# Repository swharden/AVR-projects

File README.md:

# AVR-projects
This repository contains a growing collection of individual AVR project files for various tasks. I personally use these projects as starting points for new microcontroller projects, or reference for common procedudures I would otherwise have to go back to the datasheet for (timers, counters, frequency counting or synthesis, interrupts, UART, I2C, ADC, etc). Each folder is self-contained and has batch scripts to set fuses to change the clock source (internal RC oscillator at 8MHz, div/8 for 1MHz, or external crystal typically up to 20 MHz)

**These are some of my favorites:**
> 
- Blink an LED with an [ATTiny45](/ATMega328%20%20LEDblink), [ATTiny2313](ATTiny2313%20%20LEDblink), or [ATMega328](ATMega328%20%20LEDblink)
- sending data from a microcontroller to a PC with USART (likely via USB serial port)
  - [USART for ATTiny2313](ATTiny2313%202017-02-05%20serial%20USART)
  - [ATMega328 wired](ATMega328%202015-01-01%20USART%20serial) or [over bluetooth](ATMega328%202016-09-15%20CVM)
  - [interrupt driven](ATMega328%202015-01-01%20USART%20serial/tx%20rx%20interrupt) vs. [polling method](ATMega328%202015-01-01%20USART%20serial/tx%20rx%20polling) for USART input
- [PWM for ATTiny2313](ATTiny2313%202017-02-01%20PWM) or [PWM for ATTiny85](ATTiny85%202016-12-30%20PWM)
- code to [interface with a rotary encoder](ATTiny2313%202017-02-02%20rotary%20encoder)
- ultra minimal [frequency generator](ATTiny85%202016-07-31%20frequency%20generator) I use for all sorts of stuff
- code to [read ADC values and send them over serial](ATMega328%202017-02-07%20ADC%20serial%20LM35) with ATMega328 (including code for ADC noise reduction mode)

# Programming Setup
I almost always use AVRISPmkII and AVRdude (launched from a batch script) to program my chips. I virtually never use AVRStudio. I typically develop in a Windows environment, but the code (and AVRdude) works the same in Linux.

### Software
* Just install [WinAVR](https://sourceforge.net/projects/winavr/files/) and it should install drivers for common programmers.
* I prefer to edit C code in [Notepad++](https://notepad-plus-plus.org/)
* definitely check out [AVRDudess](http://blog.zakkemble.co.uk/avrdudess-a-gui-for-avrdude/) (a GUI for AVRdude) as an easy GUI to load flash onto chips

### Hardware
* [AVR Programming in 64-bit Windows 7](http://www.swharden.com/wp/2013-05-07-avr-programming-in-64-bit-windows-7/) (should also work for windows 10)
* windows 10 driver for USBTiny is [here](https://learn.adafruit.com/usbtinyisp/drivers)
* actually I only got it to work after installing [Zadig](http://zadig.akeo.ie/)

### Programmers
Note|Picture
---|---
AVRISPmkII is a ceap, fast, and convenient AVR programmer. | 
Bus Pirate _technically_ can program AVRs, but it's so slow it's not practical. [Here's a post](http://www.swharden.com/wp/2016-07-14-controlling-bus-pirate-with-python) I wrote about it. I like the bus pirate when I need to use software to measure voltages and toggle pins. It's slow though, because the handshake it bit-banged and it takes tens of seconds to program an AVR. For just programming, I prefer an (ebay knockoff) AVR ISP mkII. Definately check out AVRDudess as a GUI for AVRDude. I usually get a standard command for a project and put it in a batch file in the same folder.| 
AVRDudess can simplify programming of code and fuses. | 

### Serial Terminal
I highly recommend [RealTerm](https://sourceforge.net/projects/realterm/) for Windows

## Common AVR Datasheets and Pinouts

chip|pinout|datasheets
---|---|---
**ATMega328**||[[summary](http://www.atmel.com/Images/Atmel-42735-8-bit-AVR-Microcontroller-ATmega328-328P_Summary.pdf)] [[complete](http://www.atmel.com/Images/Atmel-42735-8-bit-AVR-Microcontroller-ATmega328-328P_Datasheet.pdf)]
**ATTiny2313**||[[summary](http://www.atmel.com/Images/8246S.pdf)] [[complete](http://www.atmel.com/Images/doc8246.pdf)]|
**ATTiny45**||[[summary](http://www.atmel.com/Images/Atmel-2586-AVR-8-bit-Microcontroller-ATtiny25-ATtiny45-ATtiny85_Datasheet-Summary.pdf)] [[complete](http://www.atmel.com/Images/Atmel-2586-AVR-8-bit-Microcontroller-ATtiny25-ATtiny45-ATtiny85_Datasheet.pdf)]|
void waitMs1(){_delay_ms(1);}
void waitMs(int ms){while (ms-->0){waitMs1();}}
void waitSec(int sec){while (sec-->0){waitMs(1000);}}
```

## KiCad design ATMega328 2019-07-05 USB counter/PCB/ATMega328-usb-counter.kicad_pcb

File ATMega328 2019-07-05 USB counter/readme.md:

This project is now: https://github.com/swharden/USB-Counter

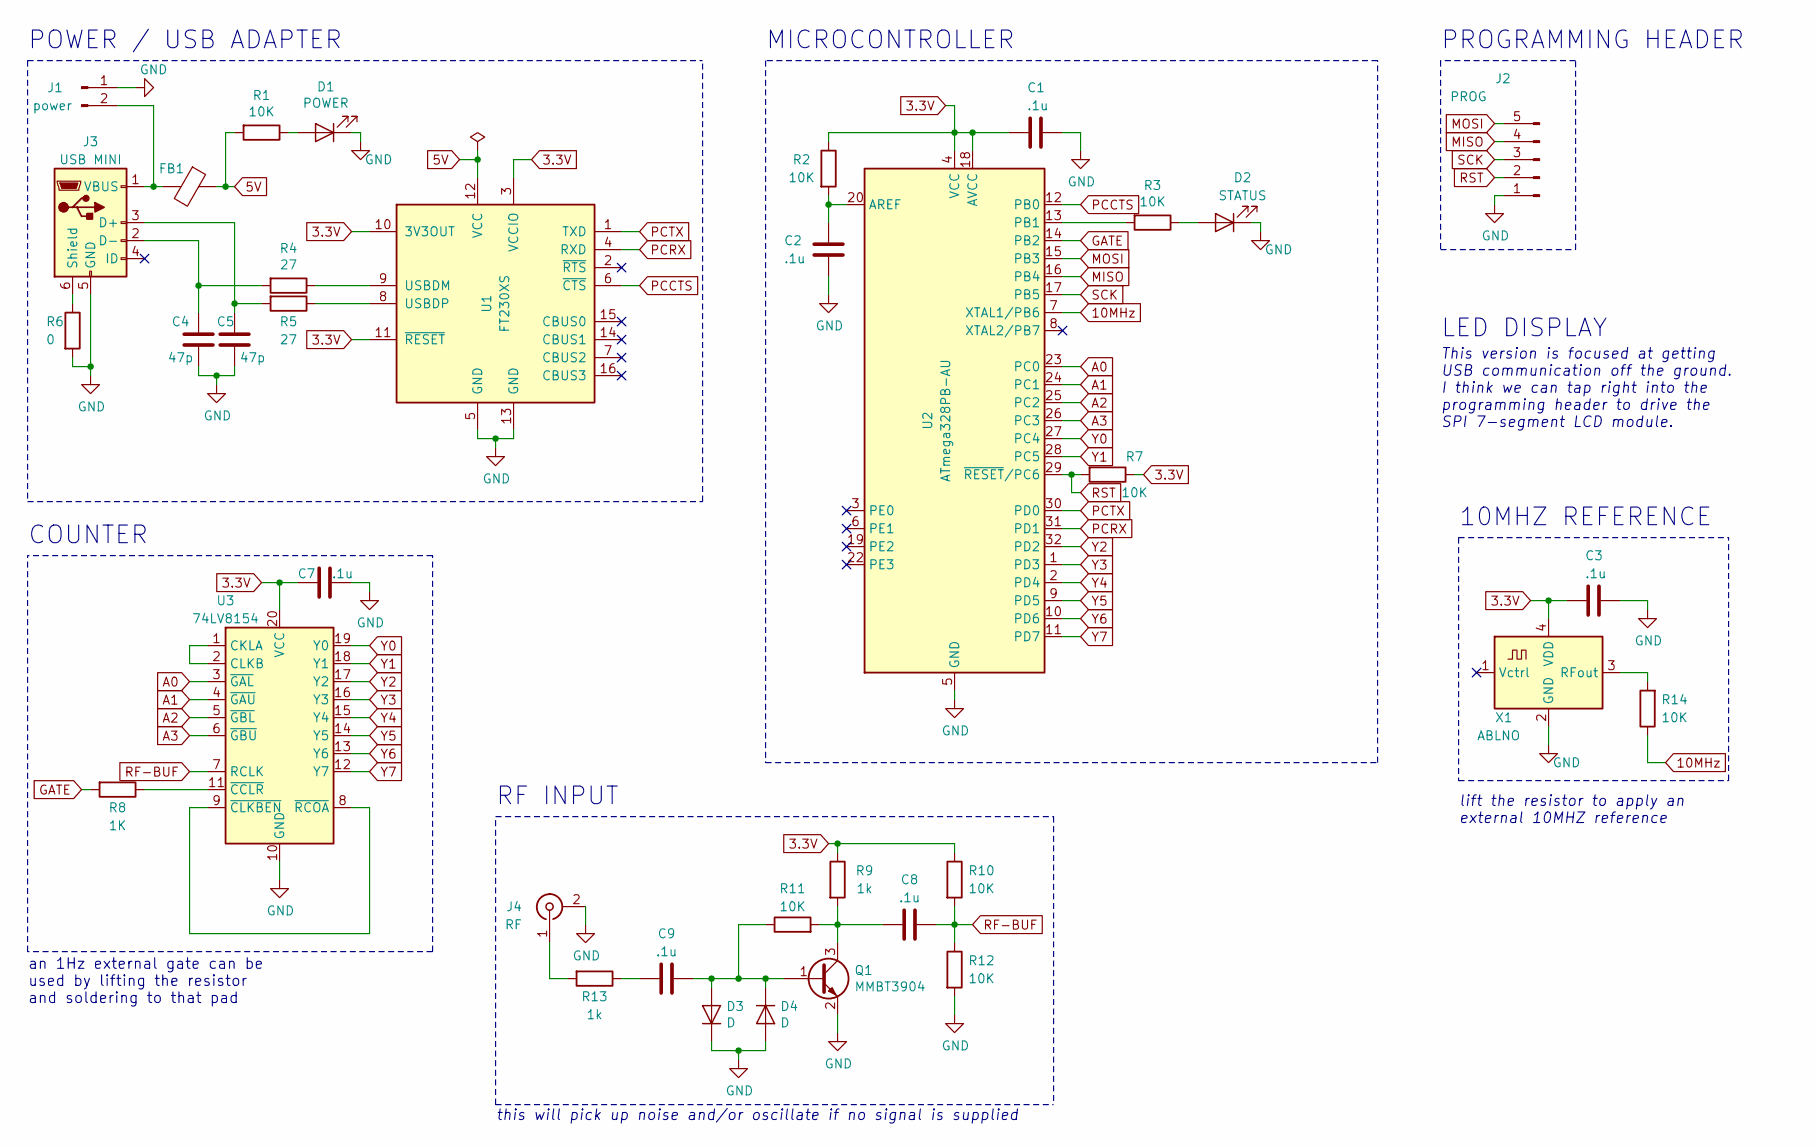
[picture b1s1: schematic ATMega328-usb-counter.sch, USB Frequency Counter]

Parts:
C1, C2, C3, C7, C8, C9: .1u; C_0805_2012Metric_Pad1.15x1.40mm_HandSolder
C4, C5: 47p; C_0805_2012Metric_Pad1.15x1.40mm_HandSolder
D1: POWER; LED_0805_2012Metric_Pad1.15x1.40mm_HandSolder
D2: STATUS; LED_0805_2012Metric_Pad1.15x1.40mm_HandSolder
D3, D4: D; D_0805_2012Metric_Pad1.15x1.40mm_HandSolder
FB1: Ferrite; R_0805_2012Metric_Pad1.15x1.40mm_HandSolder
J1: power; PinHeader_1x02_P2.54mm_Vertical
J2: PROG; PinHeader_1x05_P2.54mm_Vertical
J3: USB MINI; USB_Mini-B_Lumberg_2486_01_Horizontal
J4: RF; SMA_Amphenol_901-144_Vertical
Q1: MMBT3904; SOT-23
R1, R2, R3, R7, R10, R11, R12, R14: 10K; R_0805_2012Metric_Pad1.15x1.40mm_HandSolder
R4, R5: 27; R_0805_2012Metric_Pad1.15x1.40mm_HandSolder
R6: 0; R_0805_2012Metric_Pad1.15x1.40mm_HandSolder
R8: 1K; R_0805_2012Metric_Pad1.15x1.40mm_HandSolder
R9, R13: 1k; R_0805_2012Metric_Pad1.15x1.40mm_HandSolder
U1: FT230XS; SSOP-16_3.9x4.9mm_P0.635mm
U2: ATmega328PB-AU; TQFP-32_7x7mm_P0.8mm
U3: 74LV8154; TSSOP-20_4.4x6.5mm_P0.65mm
X1: ABLNO; Oscillator_SMD_TXC_7C-4Pin_5.0x3.2mm_HandSoldering

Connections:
3.3V: C1.1, C3.1, C7.1, R2.1, R7.1, R9.1, R10.1, U1.3 (VCCIO), U1.10 (3V3OUT), U1.11 (~RESET), U2.4 (VCC), U2.18 (AVCC), U3.20 (VCC), X1.4 (VDD)
5V: FB1.1, R1.2, U1.12 (VCC)
10MHz: R14.1, U2.7 (XTAL1/PB6)
A0: U2.23 (PC0), U3.3 (~GAL)
A1: U2.24 (PC1), U3.4 (~GAU)
A2: U2.25 (PC2), U3.5 (~GBL)
A3: U2.26 (PC3), U3.6 (~GBU)
GATE: R8.2, U2.14 (PB2)
GND: C1.2, C2.1, C3.2, C4.1, C5.1, C7.2, D1.1 (K), D2.1 (K), D3.1 (K), D4.2 (A), J1.1, J2.1, J3.5 (GND), J4.2 (Ext), Q1.2 (E), R6.2, R12.2, U1.5 (GND), U1.13 (GND), U2.5 (GND), U2.21 (GND), U3.10 (GND), X1.2 (GND)
MISO: J2.4, U2.16 (PB4)
MOSI: J2.5, U2.15 (PB3)
unnamed: C2.2, R2.2, U2.20 (AREF)
unnamed: C4.2, J3.2 (D-), R4.2
unnamed: C5.2, J3.3 (D+), R5.2
unnamed: C8.2, Q1.3 (C), R9.2, R11.2
unnamed: C9.1, D3.2 (A), D4.1 (K), Q1.1 (B), R11.1
unnamed: C9.2, R13.1
unnamed: D1.2 (A), R1.1
unnamed: D2.2 (A), R3.1
unnamed: FB1.2, J1.2, J3.1 (VBUS)
unnamed: J3.6 (Shield), R6.1
unnamed: J4.1 (In), R13.2
unnamed: R3.2, U2.13 (PB1)
unnamed: R4.1, U1.9 (USBDM)
unnamed: R5.1, U1.8 (USBDP)
unnamed: R8.1, U3.11 (~CCLR)
unnamed: R14.2, X1.3 (RFout)
unnamed: U3.1 (CKLA), U3.2 (CLKB)
unnamed: U3.8 (~RCOA), U3.9 (~CLKBEN)
PCCTS: U1.6 (~CTS), U2.12 (PB0)
PCRX: U1.4 (RXD), U2.31 (PD1)
PCTX: U1.1 (TXD), U2.30 (PD0)
RF-BUF: C8.1, R10.2, R12.1, U3.7 (RCLK)
RST: J2.2, R7.2, U2.29 (~RESET~/PC6)
SCK: J2.3, U2.17 (PB5)
Y0: U2.27 (PC4), U3.19 (Y0)
Y1: U2.28 (PC5), U3.18 (Y1)
Y2: U2.32 (PD2), U3.17 (Y2)
Y3: U2.1 (PD3), U3.16 (Y3)
Y4: U2.2 (PD4), U3.15 (Y4)
Y5: U2.9 (PD5), U3.14 (Y5)
Y6: U2.10 (PD6), U3.13 (Y6)
Y7: U2.11 (PD7), U3.12 (Y7)

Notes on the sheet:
POWER / USB ADAPTER
MICROCONTROLLER
PROGRAMMING HEADER
COUNTER
RF INPUT
this will pick up noise and/or oscillate if no signal is supplied
an 1Hz external gate can be used by lifting the resistor and soldering to that pad
This version is focused at getting USB communication off the ground. I think we can tap right into the programming header to drive the SPI 7-segment LCD module.
LED DISPLAY
10MHZ REFERENCE
lift the resistor to apply an external 10MHZ reference

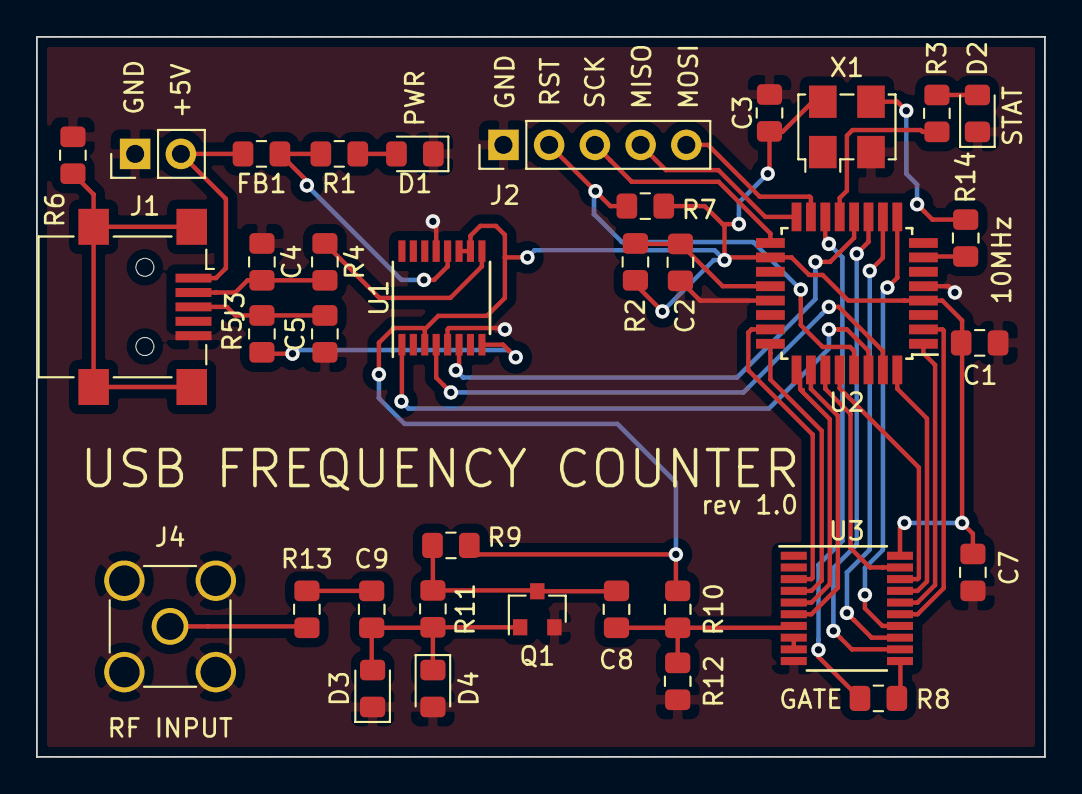
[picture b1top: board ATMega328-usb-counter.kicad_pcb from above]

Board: 2 copper layers, 56.0 x 40.0 mm, 36 parts (0 on the bottom side), 43 nets.

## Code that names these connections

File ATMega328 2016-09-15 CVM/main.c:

#define F_CPU 11059200ul

#include <avr/io.h>
#include <util/delay.h>

#define USART_BAUDRATE 9600
#define UBRR_VALUE (((F_CPU/(USART_BAUDRATE*16UL)))-1)

void serial_init(){
	// initialize USART (must call this before using it)
	UBRR0=UBRR_VALUE; // set baud rate
	UCSR0B|=(1<<TXEN0); //enable transmission only
	UCSR0C|=(1<<UCSZ01)|(1<<UCSZ01); // no parity, 1 stop bit, 8-bit data
}

void serial_send(unsigned char data){
	// send a single character via USART
	while(!(UCSR0A&(1<<UDRE0))){}; //wait while previous byte is completed
	UDR0 = data; // Transmit data
}

void serial_string(const char* s){
    while(*s){
		serial_send(*s++);
	}
}

void serial_break(){
	serial_send(10); // new line 
	serial_send(13); // carriage return
}
void serial_comma(){
	serial_send(','); // comma
	serial_send(' '); // space
}

void serial_number(uint32_t val){ // send a number as ASCII text
	uint32_t divby=1000000000; // change by dataType
	while (divby){
		serial_send('0'+val/divby);
		val-=(val/divby)*divby;
		divby/=10;
	}
}

void serial_binary(int val){ // send a number as ASCII text
	char bitPos;
	for(bitPos=8;bitPos;bitPos--){
		if ((val>>(bitPos-1))&1){serial_send('1');}
		else {serial_send('0');}
	}
}
	
void serial_test(){
	char i;
	serial_break();
	for(i=65;i<65+26;i++){
		serial_send(i);
	}
	serial_break();
}




////////////////////////////////////////////////////////////////////////
////////////////////////////////////////////////////////////////////////
////////////////////////////////////////////////////////////////////////
////////////////////////////////////////////////////////////////////////
////////////////////////////////////////////////////////////////////////
////////////////////////////////////////////////////////////////////////
////////////////////////////////////////////////////////////////////////
////////////////////////////////////////////////////////////////////////
////////////////////////////////////////////////////////////////////////
////////////////////////////////////////////////////////////////////////
////////////////////////////////////////////////////////////////////////
////////////////////////////////////////////////////////////////////////
////////////////////////////////////////////////////////////////////////

// these variables will hold an instant capture of all input pins
volatile uint8_t regB;
volatile uint8_t regC;
volatile uint8_t regD;

// these values will hold the current/voltage value
volatile char current[4];
volatile char voltage[4];


void read_capture(){
    // load the volatile capture variables with tue current pin state
    regB=PINB;
    regC=PINC;
    regD=PIND;
}

char saved_letter(){
    // returns the letter (1-8) of the segments stored in read_capture
    // returned value will be in ASCII
    // returns ? if no letter is selected, or if it's confusing
    
    // start by creating a "letter" variable which defines pin states
    uint8_t letter=0;    
    if(regD&(1<<PD0)){letter|=(1<<7);} // letter 1 (voltage MSB)
    if(regD&(1<<PD2)){letter|=(1<<6);} // letter 2
    if(regD&(1<<PD3)){letter|=(1<<5);} // letter 3
    if(regD&(1<<PD4)){letter|=(1<<4);} // letter 4
    if(regD&(1<<PD5)){letter|=(1<<3);} // letter 5 (current MSB)
    if(regD&(1<<PD6)){letter|=(1<<2);} // letter 6
    if(regD&(1<<PD7)){letter|=(1<<1);} // letter 7
    if(regB&(1<<PB0)){letter|=(1<<0);} // letter 8

    // try to match expected pin states
    if (letter==0b10000000) {return '1';}
    if (letter==0b01000000) {return '2';}
    if (letter==0b00100000) {return '3';}
    if (letter==0b00010000) {return '4';}
    if (letter==0b00001000) {return '5';}
    if (letter==0b00000100) {return '6';}
    if (letter==0b00000010) {return '7';}
    if (letter==0b00000001) {return '8';}
    return '?';    
}

volatile uint8_t saved_period;
char saved_number(){
    // returns the numerical value (0-9) stored in read_capture
    // returned value will be in ASCII
    // returns 0 if no letter is selected, or if it's confusing
    int segments=0;
    if(regC&(1<<PC5)){segments|=(1<<7);} // A (MSB)
    if(regC&(1<<PC4)){segments|=(1<<6);} // B
    if(regC&(1<<PC3)){segments|=(1<<5);} // C
    if(regC&(1<<PC2)){segments|=(1<<4);} // D
    if(regC&(1<<PC1)){segments|=(1<<3);} // E
    if(regC&(1<<PC0)){segments|=(1<<2);} // F
    if(regB&(1<<PB2)){segments|=(1<<1);} // G (LSB)
    //if(regB&(1<<PB1)){}//H
    
    if(segments==0b00001000) {return '9';}
    if(segments==0b00000000) {return '8';}
    if(segments==0b00011110) {return '7';}
    if(segments==0b01000000) {return '6';}
    if(segments==0b01001000) {return '5';}
    if(segments==0b10011000) {return '4';}
    if(segments==0b00001100) {return '3';}
    if(segments==0b00100100) {return '2';}
    if(segments==0b10011110) {return '1';}
    if(segments==0b00000010) {return '0';}
    return '?';
}

uint8_t capture_letter(char letter){
    // loops until the current letter has been captured
    uint16_t tries=1000; // trial and error reveals this works
    while (tries){
        tries--;
        read_capture(); // take a new read
        if (saved_letter()==letter) {
            if (saved_number()!='?'){
                if (letter=='1'){voltage[0]=saved_number();}
                if (letter=='2'){voltage[1]=saved_number();}
                if (letter=='3'){voltage[2]=saved_number();}
                if (letter=='4'){voltage[3]=saved_number();}
                if (letter=='5'){current[0]=saved_number();}
                if (letter=='6'){current[1]=saved_number();}
                if (letter=='7'){current[2]=saved_number();}
                if (letter=='8'){current[3]=saved_number();}
                return 1;
            }
        }
    }
    return 0;
}

void capture_full(){
    // capture even value of every letter
    char i;
    char j;
    for(i=0;i<4;i++) {voltage[i]=' ';}
    for(i=0;i<4;i++) {current[i]=' ';}
    
    for(i=0;i<8;i++){ // for each of the 8 letters
        for (j=0;j<10;j++){ // try to capture each letter 10 times
            if (capture_letter('1'+i)) {break;}
        }
    }
    
    for(i=0;i<4;i++) {
        serial_send(voltage[i]);
        if (i==1){serial_send('.');}
    }
    serial_send(',');
    for(i=0;i<4;i++) {
        serial_send(current[i]);
        if (i==2){serial_send('.');}
    }
    serial_break();
}

volatile uint16_t checksum;
int main(void){
    serial_init();
	for(;;){
        //serial_send(getDigitForLetter('1'));
        capture_full();
        //capture_letter('4');
        //serial_break();
	}
}

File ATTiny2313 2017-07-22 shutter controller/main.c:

#define F_CPU 8000000UL
#include <avr/io.h>
#include <util/delay.h>

// LED ON AND OFF FUNCTIONS
void LED_POWER_ON(){PORTD|=(1<<PD2);}
void LED_POWER_OFF(){PORTD&=~(1<<PD2);}
void LED_POWER_TOGGLE(){PORTD^=(1<<PD2);}
void LED_PV_ON(){PORTD|=(1<<PD3);}
void LED_PV_OFF(){PORTD&=~(1<<PD3);}
void LED_CF_ON(){PORTD|=(1<<PD4);}
void LED_CF_OFF(){PORTD&=~(1<<PD4);}
void LED_EN_ON(){PORTD|=(1<<PD5);}
void LED_EN_OFF(){PORTD&=~(1<<PD5);}
void LED_LASER_IN_ON(){PORTB|=(1<<PB0);}
void LED_LASER_IN_OFF(){PORTB&=~(1<<PB0);}
void LED_LASER_OUT_ON(){PORTB|=(1<<PB1);}
void LED_LASER_OUT_OFF(){PORTB&=~(1<<PB1);}

// SERVO CONTROL
// Model SG90: http://www.micropik.com/PDF/SG90Servo.pdf
// note that the servo line gets inverted
void SERVO_LOW(){PORTB|=(1<<PB2);}
void SERVO_HIGH(){PORTB&=~(1<<PB2);}

void wait(){_delay_ms(30);}
void test(){
		LED_POWER_ON();wait();
		LED_PV_ON();wait();
		LED_CF_ON();wait();
		LED_EN_ON();wait();
		LED_LASER_IN_ON();wait();
		LED_LASER_OUT_ON();wait();
		LED_POWER_OFF();wait();
		LED_PV_OFF();wait();
		LED_CF_OFF();wait();
		LED_EN_OFF();wait();
		LED_LASER_IN_OFF();wait();
		LED_LASER_OUT_OFF();wait();
}

void SHUTTER_OPEN(){
	SET_POSITION(12);
	LED_LASER_OUT_ON();
}

void SHUTTER_CLOSE(){
	SET_POSITION(18);
	LED_LASER_OUT_OFF();
}

volatile int POSITION;
void SET_POSITION(int position){
	
	// is this a new position?
	if (POSITION==position){
		return;
	} else {
		POSITION=position;
	}
	
	// position can be 10-20
	// big swings seem to be faster than small ones
	int repeats=15;
	while (repeats>0){
		LED_POWER_TOGGLE();
		int ticks = 0; // 10 ticks per ms
		SERVO_HIGH();
		while (ticks<position){
			_delay_us(96);
			ticks+=1;
		}
		SERVO_LOW();
		while (ticks<200){
			_delay_us(96);
			ticks+=1;
		}
		repeats-=1;
	}
}

void poll(){
	LED_POWER_ON();
	
	// SENSE INPUTS
	char input_PV = 0;
	char input_CF = 0;
	if (!(PINB&(1<<PB4))) input_PV=1;
	if (!(PINB&(1<<PB3))) input_CF=1;
	
	// SENSE BUTTON STATES	
	char button_PV = 0;	
	char button_CF = 0;	
	char button_EN = 0;	
	if (!(PINA&(1<<PA0))) button_PV=1;
	if (!(PINA&(1<<PA1))) button_CF=1;
	if (!(PIND&(1<<PD1))) button_EN=1;
	
	// UPDATE DISPLAY (simple)
	if (input_PV) {LED_PV_ON();} else {LED_PV_OFF();}
	if (input_CF) {LED_CF_ON();} else {LED_CF_OFF();}
	if (button_EN) {LED_EN_ON();} else {LED_EN_OFF();}
	
	// GATE LASER INPUT
	if ((input_PV && button_PV)||(input_CF && button_CF)){
		LED_LASER_IN_ON();
		if (button_EN){SHUTTER_OPEN();} else {SHUTTER_CLOSE();}
	} else {
		LED_LASER_IN_OFF();
		SHUTTER_CLOSE();
	}

}

int main(void){
	// all pins are inputs unless otherwise defined here
	DDRA=0;
	DDRB=(1<<PB0)|(1<<PB1); // LEDs
	DDRB|=(1<<PB2); // servo
	DDRD=(1<<PD2)|(1<<PD3)|(1<<PD4); // LEDs
	PORTA=(1<<PA0)|(1<<PA1); // pull buttons high
	PORTD=(1<<PD1); // pull buttons high

	// always test the LEDs when we start
	char i; for (i=0;i<3;i++){test();}

	// if all buttons are unpressed, enter a test mode
	while ((PINA&(1<<PA0))&&(PINA&(1<<PA1))&&(PIND&(1<<PD1))){
		SHUTTER_OPEN();
		test();test();
		SHUTTER_CLOSE();
		test();test();
	} 
	
	// the main program continuously polls the inputs
	for(;;){poll();}
}

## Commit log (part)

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2016-07-31 initial upload
2016-08-13 added common AVR datasheets
2016-08-14 AVR clock divider / folder restructure
2016-08-14 added pics of common chips
2016-08-14 added pinout diagrams
2016-08-15 adding pics of ckout noise
2016-09-03 clock divider
2016-09-03 usart demo
2016-09-03 folder rename
2016-09-04 sn74lv8154 32-bit counter working
2016-09-05 sn74lv8154
2016-09-05 fixed path
2016-09-09 ramp DVM
2016-09-10 serial test of big numbers
2016-09-19 current voltage meter
2016-09-19 added demo pic
2017-01-19 ATTiny85 PWM barebones example
2017-01-19 pwm screenshot
2017-01-19 deleted extra files
2017-02-03 rotary encoder
2017-02-04 Bus Pirate LM75A
2017-02-04 more advanced logging
2017-02-09 folder name
2017-02-09 excel ss
2017-02-09 Set theme jekyll-theme-leap-day
2017-02-09 Set theme jekyll-theme-cayman
2017-02-09 attiny2313 usart
2017-02-09 filename fix
2017-02-10 i2c lm75A atmega328
2017-02-12 serial reform
2017-02-12 serial reform v2
2017-02-12 polling usart
2017-04-29 lots of new projects
2017-04-29 notes
2017-08-03 shutter controller
2017-08-03 stimulus generator
2017-08-14 analog action potential generator
2017-08-14 ATMega8 AD9850 DDS
2017-08-14 reorganized old AD9850 project
2017-08-20 attiny85 LEDblink fixed
2017-08-20 microcontroller AP generator
2017-09-02 attiny85 auto-sprint
2018-01-28 fixed LEDblink links
    GitHub stopped supporting double-spaces in urls?
2018-01-28 fixed nested USART links
2018-01-28 improved datasheet links
2018-01-28 removed extra spaces breaking links
2018-02-25 nrf24L01 starting point
2018-02-25 nrf24L01 links and picture
2018-02-26 nrf24L01 works
2018-02-26 rx tx link exchanges data
2018-03-09 cleaner nrf24L01 demo
2018-03-09 fixed rx link
2018-04-25 MAX7219 LED matrix
2018-04-30 FTDI bit bang SPI
2018-05-09 ESP update
2019-02-19 reprogram for 40Hz of 5ms
2019-06-21 new laser TTL project
2019-06-22 update cache
2019-06-22 TTL controller project v2
2019-06-22 document new TTL laser controller
2019-07-06 update USB counter schematic
2019-07-06 USB counter PCB
2019-07-07 improve PCB
    higher impedance front-end, improved silkscreen
2019-07-07 document Neo-6M
2019-07-07 start QRSS TX project
2019-07-08 update QRSS TX schematic
2019-07-08 improve vFSK circuit
2019-07-08 Create CKOUT QRSS PCB (and 3D render)
2019-07-09 update crystal notes
2019-07-09 Rename readmd.md to readme.md
2019-07-10 QRSS TX update
2019-07-26 moved usb counter to own project
2019-08-04 max7219 7seg display module
2019-08-04 pull high for increased reliability
2019-09-26 i2c lcd backpack documentation
2020-08-31 add note about line termination
    #2
2020-08-31 add links to newer USB counter project
2022-11-16 Arduino: LED blink
2022-11-16 Arduino: HX710B pressure sensor
2022-11-16 Arduino: scan I2C devices
2022-11-16 Arduino: BMP280
2022-11-30 bmp280: temperature calibration works
2022-12-08 ATTiny826 LED blink
2022-12-16 ATTiny826: clock
2022-12-17 ATTiny826: 1pps timer
2022-12-17 improve folder names
2022-12-17 ATTiny826 1pps: clear interrupt flag
2022-12-17 ATTiny826 1pps: use 10mhz reference
2022-12-17 ATTiny826: serial
2022-12-17 ATTiny826 counter
    close but output is not stable... unsynchronized clock sources?
2022-12-18 ATTiny826 counter: improve accuracy
2022-12-24 Arduino HX710: support new IDE
2022-12-25 Arduino PWM: readme
2023-01-03 AVR64DD32 LEDblink
2023-01-04 AVR64DD32 serial
2023-01-05 AVR64DD32
2023-01-05 AD64DD32 comparator
2023-01-05 AVRDD32 counter
    TCD0 is counting something but they aren't events
2023-01-14 MCP3201
2023-01-15 FT232H SPI ADC
2023-01-15 FT232H SPI
2023-01-17 benchmark
2023-01-17 Arduino ADS1115
2023-01-17 move nested folders
2023-01-17 add empty readmes to top-level folders
2023-01-17 Arduino LM75A
2023-01-18 FT232H I2C works
2023-01-18 refactor communicator classes
2023-01-24 FT232H I2C address scanning
2023-05-23 BMP280 temperature and pressure sensor
2023-05-24 ESP8266 notes
2023-05-24 NodeMCU 12E notes
2023-05-24 NodeMCU BMP280
2023-05-24 NodeMCU weather station
2023-08-15 weather: update code
2023-08-15 attiny826 pwm
2023-08-16 ATTiny826 speech
2023-08-16 ATTiny826 speech: fix audio sample rate
2023-08-16 AVR64DD: speech
2023-08-20 Arduino speech
2023-08-26 Arduino SPI audio
2023-08-26 AVRDD6432 speech and music
2023-08-26 AVR64DD32 SPI audio
2023-08-29 AVR64DD32 counter: uses system clock
2023-08-29 AVR64DD32: external clock frequency counter
2023-08-29 AVR64DD32: improve counter accuracy
2023-08-29 improve counter precision
2023-08-29 AVR64DD32 talking frequency meter
2023-08-29 gate counter using RTC period
2023-08-29 improve talking counter
2023-08-30 improve audio number readout
2023-08-30 improve voice output
2023-08-30 add button
2023-08-31 use DAC for audio output
2023-08-31 AVR64DD32: improve frequency counter
2023-09-07 AVR64DD32 7-segment display
2023-09-08 AVR64DD32 ADC
2023-09-08 differential ADC
